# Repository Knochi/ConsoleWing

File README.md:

# ConsoleWing
a mobile console to held your feather + wings

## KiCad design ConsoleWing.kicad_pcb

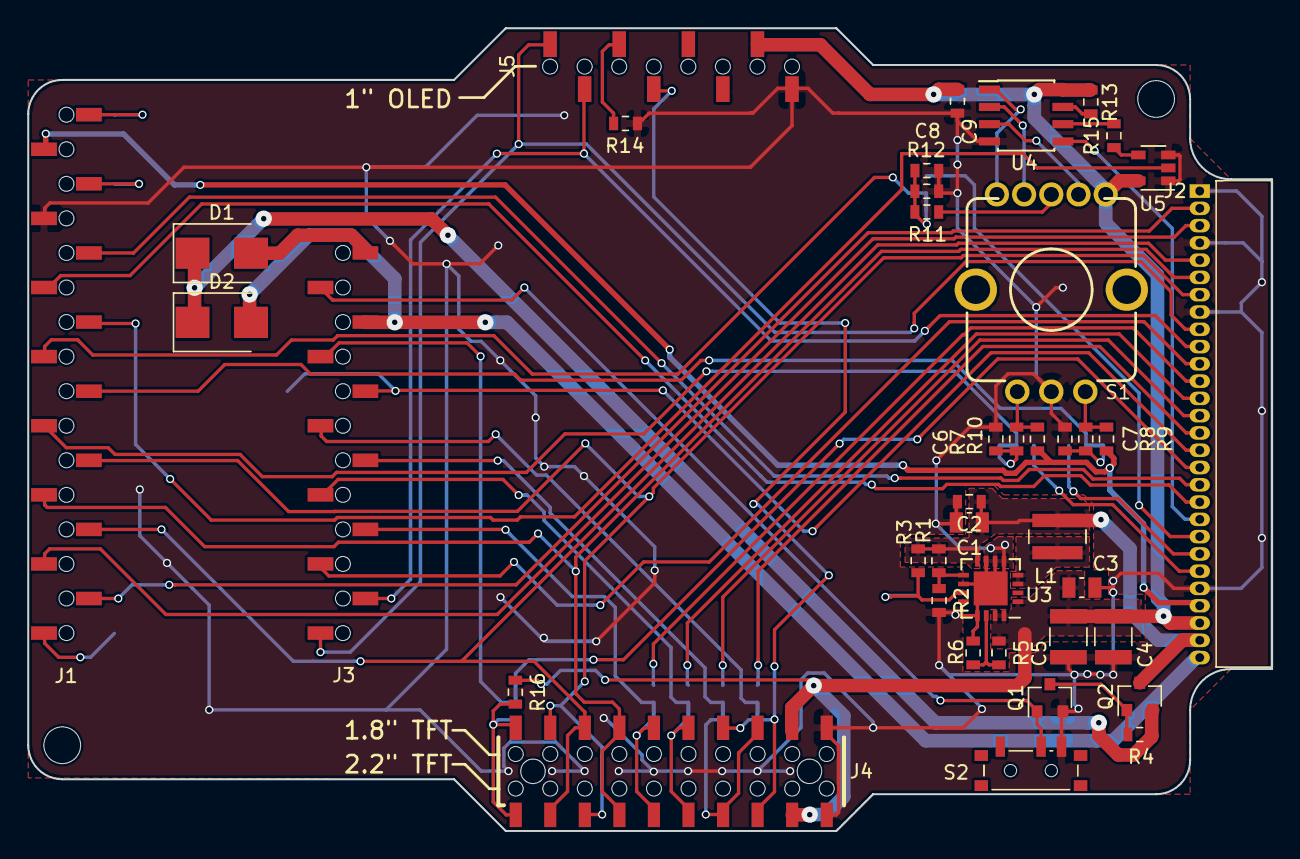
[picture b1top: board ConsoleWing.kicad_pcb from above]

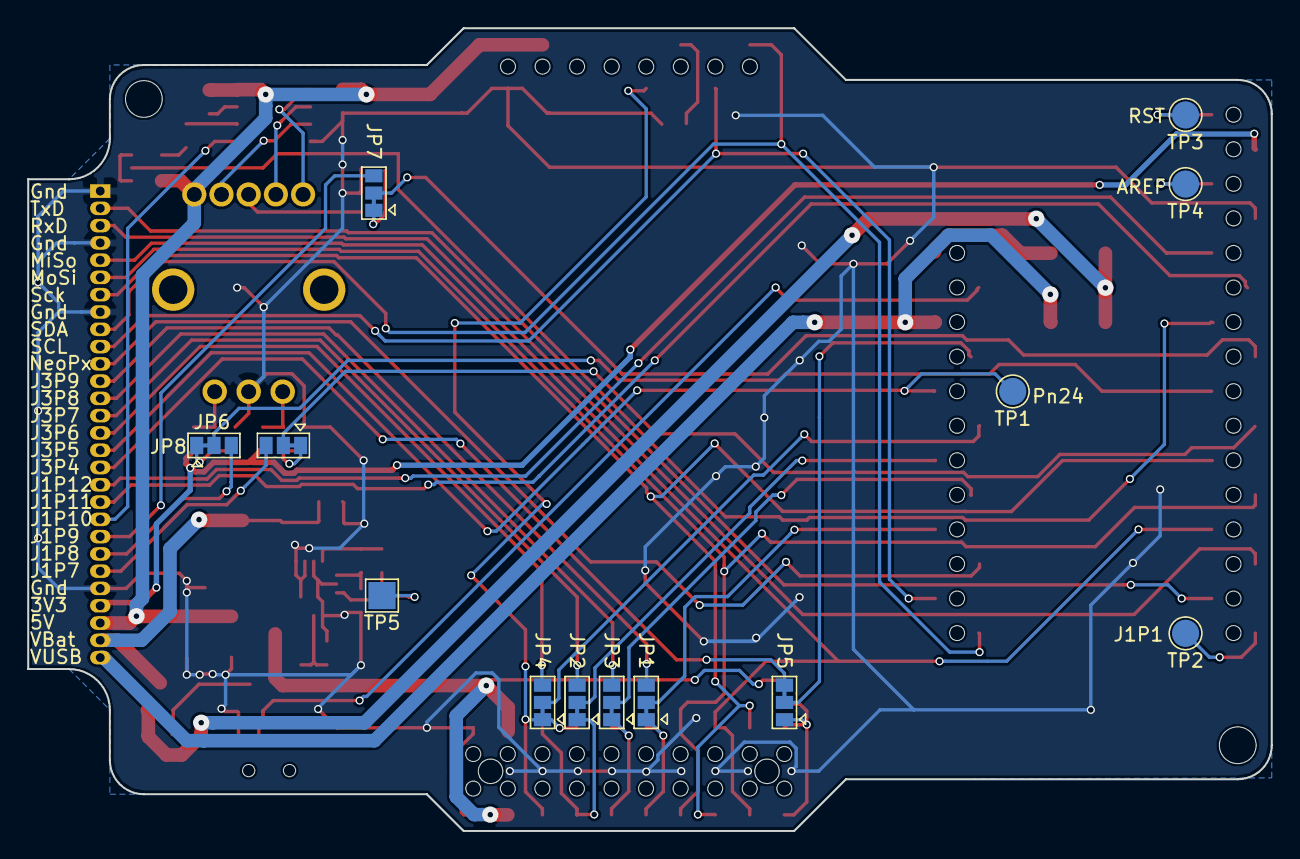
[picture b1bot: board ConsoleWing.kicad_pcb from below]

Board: 2 copper layers, 91.4 x 59.0 mm, 53 parts (13 on the bottom side), 63 nets.

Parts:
C1: 10uF; C_0805_2012Metric
C2: 0.1uF; C_0603_1608Metric
C3: 2.2uF; C_0805_2012Metric
C4, C5: 100uF; C_1210_3225Metric
C6, C7, C8: 10n; C_0603_1608Metric
C9: 100n; C_0603_1608Metric
D1, D2: NRVBS360T3G; D_SMB
J1: CONN_01X16; 098-1-016
J2: CONN_01X28; PinHeader_1x28_P1.27mm_Horizontal_Series204
J3: CONN_01X12; 098-1-012
J4: CONN_02X10; 098-3-020
J5: CONN_01X08; 098-1-008
JP1, JP2, JP3, JP4, JP6, JP7, JP8: NCNO; SolderJumper_01x03_NCNO
JP5: NONC; SolderJumper_01x03_NONC
L1: 6.8uH; L_Wuerth_MAPI-4030
Q1: BSS138; SOT-23
Q2: DMG3415U; SOT-23
R1: 2M; R_0603_1608Metric
R2: 480k; R_0603_1608Metric
R3, R4: 100k; R_0603_1608Metric
R5: 1.6M; R_0603_1608Metric
R6: 180k; R_0603_1608Metric
R7, R8, R9, R10, R11: 10k; R_0603_1608Metric
R12: 15k; R_0603_1608Metric
R13, R14: 0r; R_0603_1608Metric
R15: 22r; R_0603_1608Metric
R16: 1k; R_0603_1608Metric
S1: ENCODER-RGB-SWITCH; ENCODER_LED_3
S2: PowerOnOff; SW_SPDT_PCM12
TP1: Pn24; TestPoint_Pad_D2.0mm
TP2: J1P1; TestPoint_Pad_D2.0mm
TP3: RST; TestPoint_Pad_D2.0mm
TP4: AREF; TestPoint_Pad_D2.0mm
TP5: TEST; TestPoint_Pad_2.0x2.0mm
U3: TPS6103x; QFN-16-1EP_4x4mm_P0.65mm
U4: WS2811; SOIC-8_3.9x4.9mm_P1.27mm
U5: SN74AHCT1G125; SOT-23-5

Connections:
+3V3: J1.15, J2.25, R9.2, R10.2
+5V: C3.1, C4.1, C5.1, C9.1, J2.26, J4.17, J4.18, J5.7, R5.1, R13.1, R16.1, S1.5, U3.1, U3.15, U3.16, U4.8, U5.5
+BATT: D1.2, J3.1
+BATT_SW: C1.1, C2.1, J2.27, L1.1, Q2.3, R1.1, R3.1, U3.8
/Displays/TFT_CS: J4.9, J4.10, JP1.1
/Displays/TFT_DC: J4.13, J4.16, JP2.1
/Displays/TFT_LITE: J4.1, J4.2, JP5.1, R16.2
/Displays/TFT_RST: J4.14, J4.15, J5.4, JP4.1
/Displays/uSD_CS: J4.11, J4.12, JP3.1
/FTH_J1P1: J1.1, TP2.1
/FTH_J1P7: J2.23, JP6.3
/FTH_J1P8: J2.22, JP8.3
/FTH_J1P9: J2.21, JP7.3
/FTH_J1P11: J1.11, J2.19
/FTH_J1P12: J1.12, J2.18
/FTH_J3P4: J2.17, JP5.3
/FTH_J3P5: J2.16, J3.5, TP1.1
/FTH_J3P6: J2.15, JP4.3
/FTH_J3P7: J2.14, JP2.3
/FTH_J3P8: J2.13, JP3.3
/FTH_J3P9: J2.12, JP1.3
/FTH_J3P10: J2.11, J3.10
/FTH_RST: J1.16, TP3.1
/NeoPx_In: J1.10, U5.2
/NeoPx_Out: J2.20, U4.5
/Power/VBATT_VUSB: D1.1, D2.1, Q2.2, R4.2
/Power/~ENABLE~: Q1.3, Q2.1, R4.1
/Rotary Encoder/ENC_SW: R11.2, S1.3
/Rotary Encoder/EncA: C6.1, JP6.1, R7.2
/Rotary Encoder/EncB: C7.1, JP8.1, R8.2
/Rotary Encoder/EncBtn: C8.1, JP7.1, R11.1, R12.2
/Rotary Encoder/NeoPx_In_5V: R15.2, U4.6
ENABLE: J3.2, Q1.1, S2.2
GND: C1.2, C2.2, C3.2, C4.2, C5.2, C6.2, C7.2, C8.2, C9.2, J1.13, J2.1, J2.4, J2.8, J2.24, J4.19, J4.20, J5.8, Q1.2, R2.2, R6.2, R12.1, R14.2, S1.C, S2.3, U3.5, U3.6, U3.7, U3.10, U3.13, U3.17, U4.4, U5.1, U5.3
MISO: J1.4, J2.5, J4.3, J4.6
MOSI: J1.5, J2.6, J4.7, J4.8
unnamed: J1.7, JP6.2
unnamed: J1.8, JP8.2
unnamed: J1.9, JP7.2
unnamed: J1.14, TP4.1
unnamed: J3.4, JP5.2
unnamed: J3.6, JP4.2
unnamed: J3.7, JP2.2
unnamed: J3.8, JP3.2
unnamed: J3.9, JP1.2
unnamed: J5.3, R14.1
unnamed: R1.2, R2.1, U3.9
unnamed: R3.2, TP5.1, U3.11
unnamed: R5.2, R6.1, U3.14
unnamed: R8.1, R9.1, S1.B
unnamed: R7.1, R10.1, S1.A
unnamed: R13.2, U4.7
unnamed: R15.1, U5.4
unnamed: S1.1, U4.1
unnamed: S1.2, U4.2
unnamed: S1.4, U4.3
RxD: J1.3, J2.3
SCK: J1.6, J2.7, J4.4, J4.5
SCL: J2.10, J3.11, J5.2
SDA: J2.9, J3.12, J5.1
SW: L1.2, U3.3, U3.4
TxD: J1.2, J2.2
VUSB: D2.2, J2.28, J3.3

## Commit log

2019-11-08 renamed and initial upload
2019-11-08 add housing
